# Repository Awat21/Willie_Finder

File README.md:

# Willie_Finder
Cat tracker using LORA

- [BOM.md](BOM.md) - parts list with links
- [case/](case/) - collar pod case model (STEP, STL, CadQuery source)
- [pcb/](pcb/) - custom single-board tracker: schematic and first-pass layout (KiCad 9)

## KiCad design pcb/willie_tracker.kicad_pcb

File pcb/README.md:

# Custom tracker PCB

Draft schematic (rev 0.4) and a first-pass board layout for a single-board version of the collar tracker. **Not ready for fabrication.**

- `willie_tracker.kicad_sch`, `willie_tracker.kicad_pro`, `sym-lib-table` - KiCad 9 project (needs KiCad 9 or newer).
- `willie_tracker.pdf` - the same schematic as a PDF.
- `willie.kicad_sym` - project symbol library (RAK4630).
- `gen_schematic.py`, `sexpr.py` - generator; the parts and net table at the top of `gen_schematic.py` are the source.
- `willie_tracker.net` - netlist exported by KiCad from the schematic.
- `check_netlist.py` - regenerates, exports the netlist with `kicad-cli`, compares it to the net table, checks the stacked pads, runs ERC and exports the PDF.
- `erc_report.txt` - KiCad's electrical rule check report.
- `willie_tracker.kicad_pcb` - first-pass board layout (KiCad 9).
- `willie.pretty/RAK4630.kicad_mod`, `fp-lib-table` - RAK4630 land pattern, drawn from RAK's datasheet drawings.
- `gen_layout.py` - places the parts (the placement table at the top is the source). `route.py` - grid autorouter with rip-up and re-route. Run both with the Python that has KiCad's `pcbnew` module: `/usr/bin/python3 route.py`.
- `drc_report.txt` - KiCad's design rule check report for the layout.
- `willie_tracker_board.step` - bare board (outline and holes, no component bodies) for CAD.
- `renders/` - top and bottom views of the board.

## What is on it

| Block | Part | Notes |
|---|---|---|
| MCU + LoRa + Bluetooth | RAK4630 (-I variant with U.FL sockets) | Same pins as the Meshtastic `rak4631` variant |
| GNSS | u-blox MAX-M10S, U.FL socket for a passive antenna | UART on P0.15/P0.16, PPS on P0.17 |
| GNSS power switch | TPS22917 | Enabled by P1.02 (the firmware's `PIN_3V3_EN`) |
| Accelerometer | LIS3DH, I2C 0x18 | INT1 on P1.01 |
| Charger and power path | MCP73871, 100 mA USB input limit | Runs the system from USB while charging; battery supplements peaks. Amber LED while charging |
| Regulator | XC6220 3.3 V | Fed from VSYS (USB when plugged in, otherwise the battery) |
| GNSS signal buffer | 74LVC3G34 on the switched rail | Isolates TX, RX and PPS when the GNSS is off |
| Battery sense | 1M / 1.5M divider on P0.05 | Matches the RAK base boards |
| USB | GCT USB4110 USB-C (all surface-mount) with CC resistors and USBLC6 ESD protection | Charging and firmware updates |

## Review status (rev 0.3)

Response to the rev 0.2 schematic review:

| Finding | Status |
|---|---|
| 1. U6 and U7 ground pads unverified | Verified in the native netlist (`willie_tracker.net`, exported by KiCad): U6.1, U6.10, U6.12, U7.5, U7.10 and U7.12 are all on GND. `check_netlist.py` now asserts these and the other stacked pads on every run, and the schematic lists the stacked pins in a note. The library footprints (`RF_GPS:ublox_MAX`, `Package_LGA:LGA-16_3x3mm_P0.5mm_LayoutBorder3x5y`) contain pads 1-18 and 1-16. ERC has since been run; see below. |
| 2. USB inrush and current budget | Changed: the MCP73831 and the discrete load sharing are replaced by an MCP73871 power-path charger. SEL and PROG2 are tied low, which limits total USB input current to 100 mA (80-100 mA per the datasheet). Above that the battery supplements the load through the internal ideal diode. Only C1 (4.7 uF) is directly on VBUS; C3 is behind the current limit. |
| 3. Battery handover and VBUS leakage | Removed with the discrete circuit: Q1, D3 and R13 are gone. Handover is inside the MCP73871. |

Earlier fixes kept: regulator capacitors (10 uF / 4.7 uF), GNSS buffer U8, passive-antenna note.

MCP73871 pin settings, checked against Microchip DS20002090E: SEL low = USB input; PROG2 low = 100 mA; THERM 10k to VSS = no thermistor; VPCC tied to IN = disabled; TE low = safety timer enabled; CE high = charging enabled; PROG1 13k = 77 mA; PROG3 100k = 10 mA termination.

## Board layout (first pass)

| | |
|---|---|
| Size | 25.0 x 44.0 mm rectangle, 0.8 mm thick |
| Assembly | Every part is surface-mount and on the top side. The bottom is bare, so the board can sit flat on a hot plate |
| Through-holes | No plated through-hole pads. Two unplated locating holes for the USB-C connector's pegs |
| Layers | 4: top (parts and signals), inner 1 (solid ground plane), inner 2 (signals plus a 3.3 V pour), bottom (signals plus a ground pour) |
| Assembled thickness | About 4 mm: USB-C connector roughly 3.2 mm on a 0.8 mm board (estimate from datasheet heights) |
| Rules | 0.2 mm tracks, 0.15 mm clearance, 0.6 / 0.3 mm vias, tented |
| Routing | 933 track segments, 146 vias, every net connected |
| KiCad DRC | 0 errors, 0 unconnected pads, 0 schematic parity issues, 1 library-sync warning on J1 (`drc_report.txt`) |

Changes for single-sided assembly (schematic rev 0.4):

- USB-C connector is now the GCT USB4110 (all surface-mount shell tabs) instead of a part with through-hole legs.
- The battery leads solder to two 1.5 x 3 mm surface pads (J2 BAT+, J4 BAT-) instead of through-hole wire pads.
- The five test pads moved to the top side.
- Length grew from 40 to 44 mm, the top of the allowed range, to give the small parts room for their vias.

The routing was done by `route.py`, a simple autorouter written for this board. It satisfies the clearance rules but
has had no engineering review. Before fabrication:

1. All tracks are 0.2 mm, including power (VBUS, VSYS, +BATT, +3V3). Widen the power tracks.
2. GNSS_RF is a short 0.2 mm track, not a calculated 50 ohm line. Set its width from the board house's stackup.
3. Tracks and tented vias run under the RAK4630. Check RAK's layout guidance for keep-out areas under the module.
4. Decoupling capacitors were placed for fit, not for shortest loop to their pins. Review each one.
5. USB D+ and D- are routed as two ordinary tracks, not a matched pair. Acceptable at full speed over this length; confirm.
6. Ground is poured on inner layer 1 and the bottom; the top has no pour. The 3.3 V pour on inner layer 2 is broken up by signal tracks.
7. The RAK4630 land pattern was drawn from the dimensions in RAK's datasheet images. Check it against a real module or RAK's own footprint before ordering.
8. Reference designators are hidden on the silkscreen; there is no silkscreen artwork, fiducials or mounting features.
9. USB-C sits at one short edge; the connector's exact overhang past the board edge is not checked.
10. Check that the USB4110's locating pegs do not stick out below a 0.8 mm board; if they do, the board will not sit flat on a hot plate (use a thicker board or trim the pegs).
11. Surface-mount battery pads can peel under wire strain. Glue or otherwise strain-relieve the leads.
12. The render shows via rings exposed although tenting is set in the board file; confirm in the Gerbers.
13. Tracks and vias also run under the MAX-M10S; check u-blox's layout guidance for the area under the module.
14. The J1 library-sync warning in DRC is unexplained; the pads and nets match the schematic.

## Electrical rule check

Run with `kicad-cli` 9.0.9, all severities. Two items remain, both intended:

| Item | Severity | Explanation |
|---|---|---|
| U4 QOD (open collector) tied to VOUT (power output) | error | Confirmed against TI's TPS22917 datasheet (section 9.3.3): shorting QOD to VOUT is one of the three documented configurations and uses the internal discharge resistance. CT left open is also a documented option. KiCad flags the pin types only. |
| U7 SDO/SA0 (bidirectional) on GND | warning | Intended: address-select pin tied low for I2C address 0x18. |

No unconnected pins, undriven power pins or conflicting outputs were reported.

## Confirmed since rev 0.3

- TPS22917 QOD to VOUT: confirmed (above). Its DBV pinout in the datasheet matches the KiCad symbol.
- RAK4630 supply pins: RAK's reference schematic states that for a single 3.3 V supply VBAT_NRF, VDD_NRF, VBAT_SX and VBAT_IO_SX are all connected to 3.3 V, as drawn here.
- RAK4630 pin order: RAK's pinout drawing matches the land pattern (pin 1 at the top-right of the top row, counting anticlockwise).
- VBUS capacitance: RAK's schematic shows a 4.7 uF capacitor on VBUS inside the module. With C1 that is 9.4 uF nominal directly on VBUS, just under the 10 uF limit.

## Open items

1. USB charge current: the datasheet says PROG1 sets fast charge when SEL is high. With SEL low the charge current may follow the 100 mA USB limit rather than the 77 mA resistor setting. Confirm, and check either value against the chosen cell's rating.
2. Charger variant: -2CC is a first pick (4.20 V). Confirm its timer period and low-battery-indicator options.
3. VBUS capacitance is 9.4 uF nominal against a 10 uF limit; decide whether to reduce C1.
4. With USB connected the regulator input (VSYS) follows VBUS, about 5 V. Confirm against the XC6220 rating.
5. U8 relies on the 74LVC family's powered-off protection. The review confirmed this for the Nexperia part; use that manufacturer or re-check.
6. LIS3DH unused ADC pins are tied to ground; confirm against the datasheet.
7. The layout items listed under "Board layout" above.

## To verify on a prototype

- Charge termination with the tracker running on USB, and USB attach, detach and cold boot on each kind of port you intend to support (including a plain USB 2.0 port or hub).
- The 3.3 V rail on a scope with a partly discharged cell during GNSS startup, LoRa transmit, and both together.
- GNSS RX pin voltage and switched-rail current with the GNSS off, during reset, and across several on/off cycles. Confirm 3V3_GNSS discharges on shutdown and that UART and PPS behave through power transitions.
- GNSS reception with the actual passive antenna in the enclosure; route GNSS_RF as a 50 ohm trace.

## Firmware checks

- GNSS enable is expected active-high on Arduino pin 34 (P1.02); confirm with the intended Meshtastic build.
- Battery reading: the 1M / 1.5M divider is nominally x1.667 and the RAK4631 firmware uses x1.73, so a 4.20 V cell may read about 0.16 V high. Calibrate against a meter.
- LIS3DH INT1 is wired to P1.01, but the stock Meshtastic driver polls over I2C. Wake-on-motion from deep sleep needs firmware support.

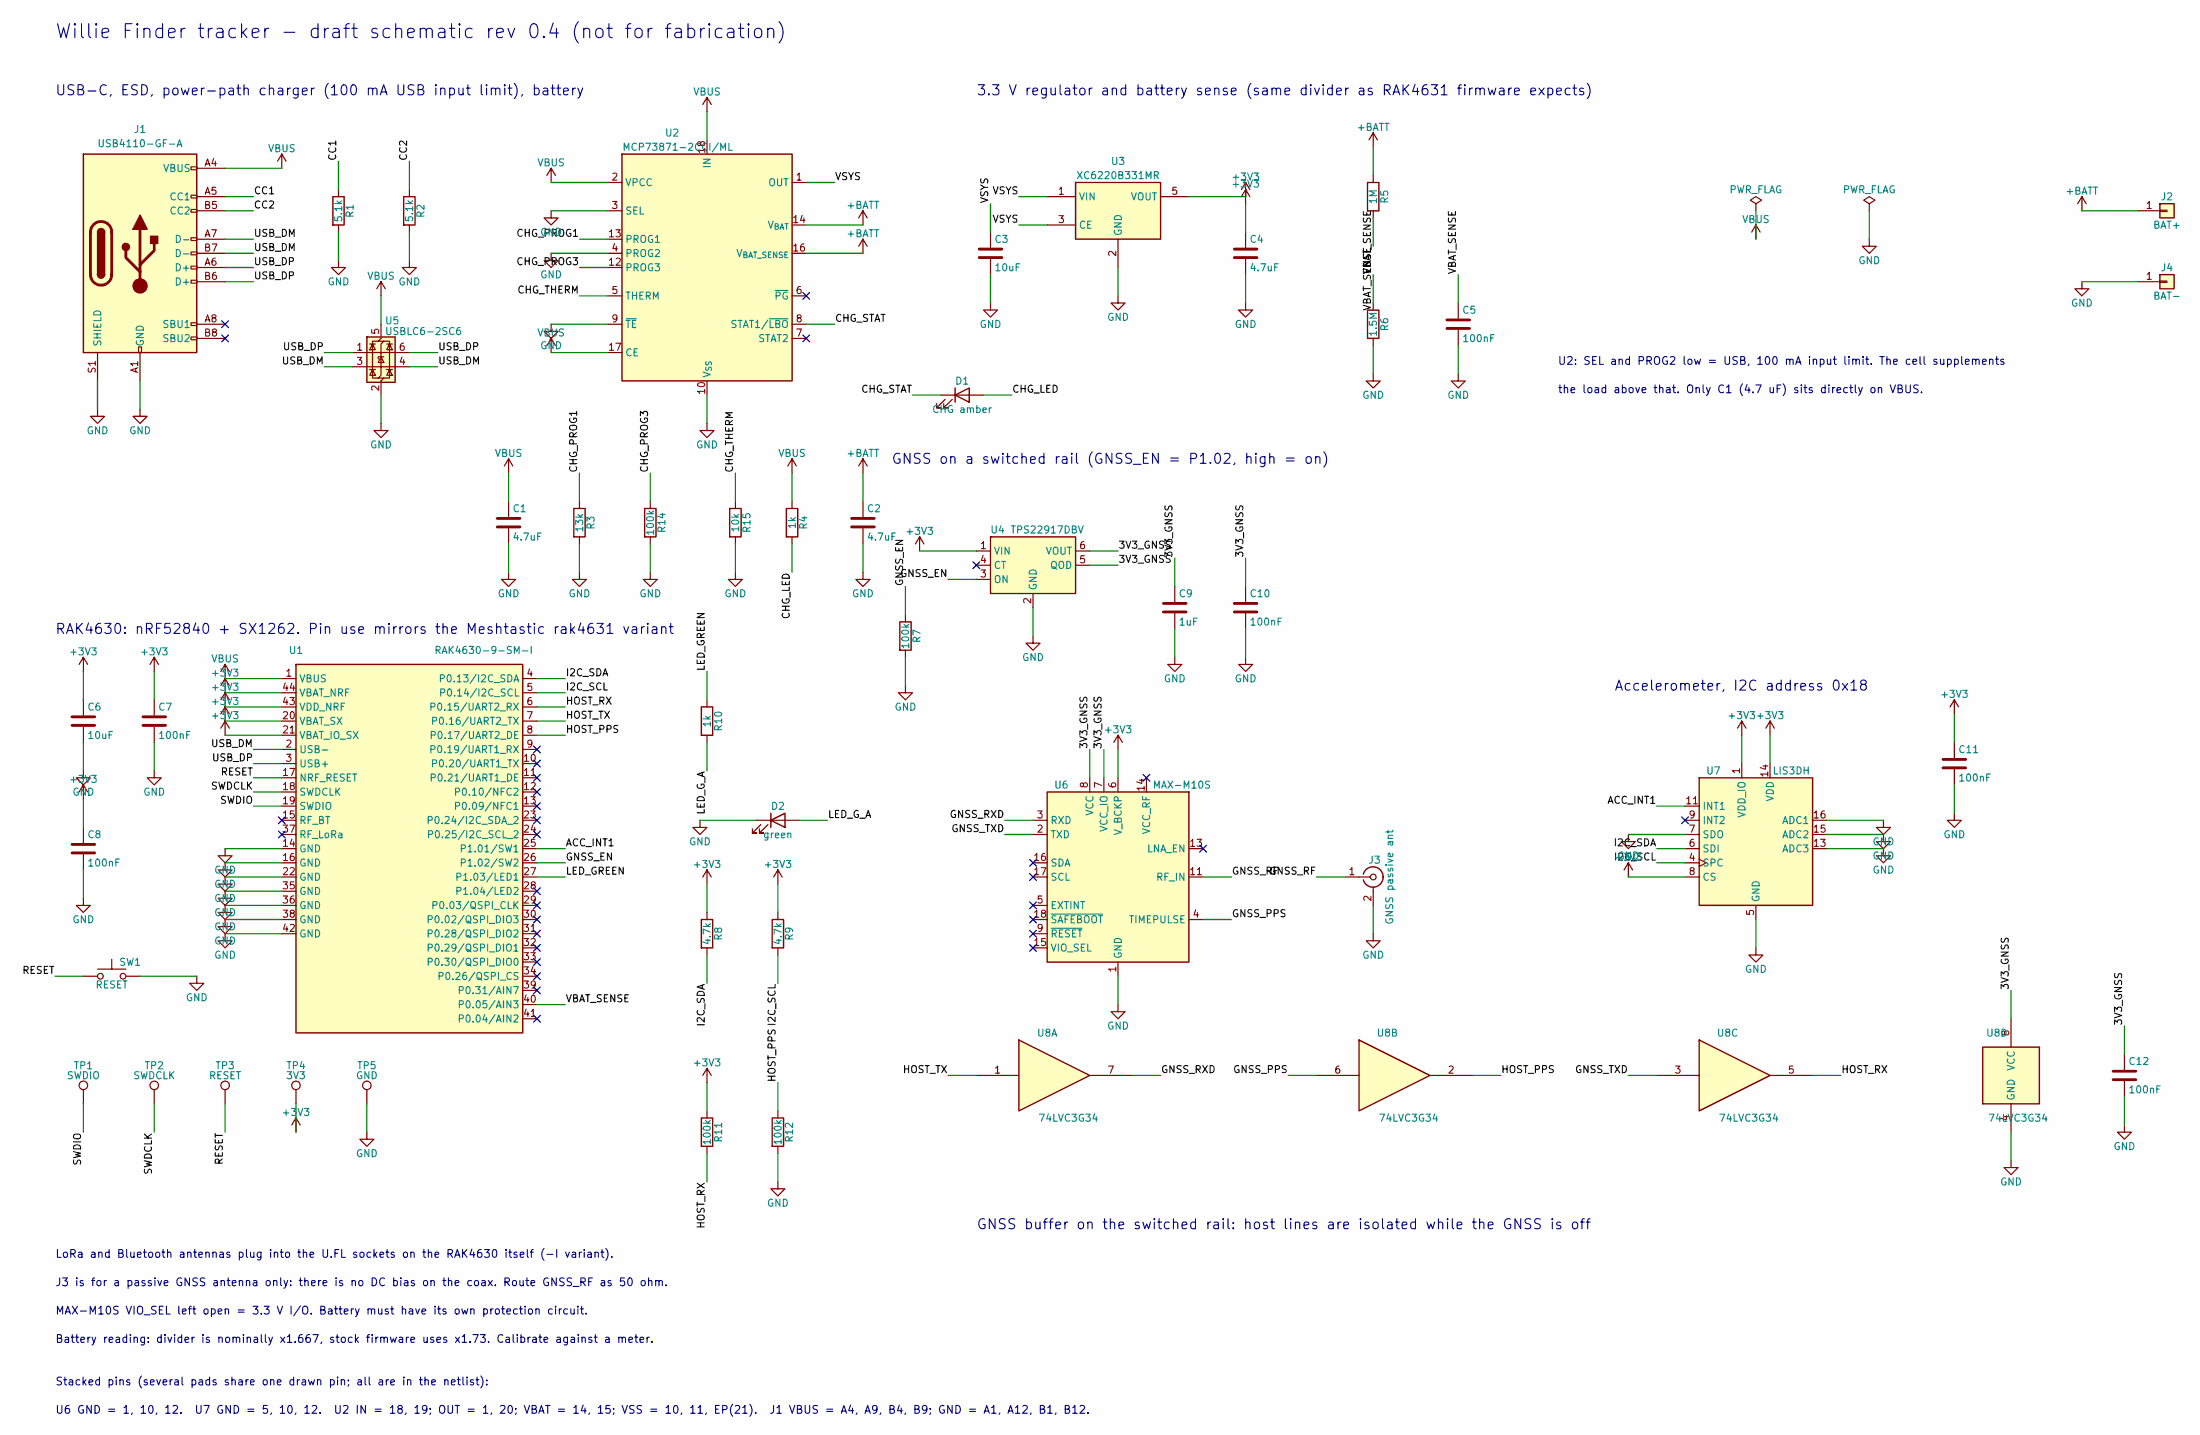
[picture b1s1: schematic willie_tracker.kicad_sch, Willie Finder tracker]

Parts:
C1, C2: 4.7uF; C_0603_1608Metric
C3, C6: 10uF; C_0603_1608Metric
C4: 4.7uF; C_0402_1005Metric
C5, C7, C8, C10, C11, C12: 100nF; C_0402_1005Metric
C9: 1uF; C_0402_1005Metric
D1: CHG amber; LED_0402_1005Metric
D2: green; LED_0402_1005Metric
J1: USB4110-GF-A; USB_C_Receptacle_GCT_USB4110
J2: BAT+; SolderWirePad_1x01_SMD_1.5x3mm
J3: GNSS passive ant; U.FL_Hirose_U.FL-R-SMT-1_Vertical
J4: BAT-; SolderWirePad_1x01_SMD_1.5x3mm
R1, R2: 5.1k; R_0402_1005Metric
R3: 13k; R_0402_1005Metric
R4, R10: 1k; R_0402_1005Metric
R5: 1M; R_0402_1005Metric
R6: 1.5M; R_0402_1005Metric
R7, R11, R12, R14: 100k; R_0402_1005Metric
R8, R9: 4.7k; R_0402_1005Metric
R15: 10k; R_0402_1005Metric
SW1: RESET; SW_SPST_B3U-1000P
TP1: SWDIO; TestPoint_Pad_D1.0mm
TP2: SWDCLK; TestPoint_Pad_D1.0mm
TP3: RESET; TestPoint_Pad_D1.0mm
TP4: 3V3; TestPoint_Pad_D1.0mm
TP5: GND; TestPoint_Pad_D1.0mm
U1: RAK4630-9-SM-I; RAK4630
U2: MCP73871-2CCI/ML; QFN-20-1EP_4x4mm_P0.5mm_EP2.5x2.5mm
U3: XC6220B331MR; SOT-23-5
U4: TPS22917DBV; SOT-23-6
U5: USBLC6-2SC6; SOT-23-6
U6: MAX-M10S; ublox_MAX
U7: LIS3DH; LGA-16_3x3mm_P0.5mm_LayoutBorder3x5y
U8: 74LVC3G34; VSSOP-8_2.3x2mm_P0.5mm

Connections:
+3V3: C4.1, C6.1, C7.1, C8.1, C11.1, R8.1, R9.1, R11.1, TP4.1, U1.20 (VBAT_SX), U1.21 (VBAT_IO_SX), U1.43 (VDD_NRF), U1.44 (VBAT_NRF), U3.5 (VOUT), U4.1 (VIN), U6.6 (V_BCKP), U7.1 (VDD_IO), U7.8 (CS), U7.14 (VDD)
+BATT: C2.1, J2.1, R5.1, U2.14 (V_{BAT}), U2.15 (V_{BAT}), U2.16 (V_{BAT_SENSE})
/3V3_GNSS: C9.1, C10.1, C12.1, U4.5 (QOD), U4.6 (VOUT), U6.7 (VCC_IO), U6.8 (VCC), U8.8 (VCC)
/ACC_INT1: U1.25 (P1.01/SW1), U7.11 (INT1)
/CC1: J1.A5 (CC1), R1.1
/CC2: J1.B5 (CC2), R2.1
/CHG_LED: D1.2 (A), R4.2
/CHG_PROG1: R3.1, U2.13 (PROG1)
/CHG_PROG3: R14.1, U2.12 (PROG3)
/CHG_STAT: D1.1 (K), U2.8 (STAT1/~LBO)
/CHG_THERM: R15.1, U2.5 (THERM)
/GNSS_EN: R7.1, U1.26 (P1.02/SW2), U4.3 (ON)
/GNSS_PPS: U6.4 (TIMEPULSE), U8.6
/GNSS_RF: J3.1 (In), U6.11 (RF_IN)
/GNSS_RXD: U6.3 (RXD), U8.7
/GNSS_TXD: U6.2 (TXD), U8.3
/HOST_PPS: R12.1, U1.8 (P0.17/UART2_DE), U8.2
/HOST_RX: R11.2, U1.6 (P0.15/UART2_RX), U8.5
/HOST_TX: U1.7 (P0.16/UART2_TX), U8.1
/I2C_SCL: R9.2, U1.5 (P0.14/I2C_SCL), U7.4 (SPC)
/I2C_SDA: R8.2, U1.4 (P0.13/I2C_SDA), U7.6 (SDI)
/LED_GREEN: R10.1, U1.27 (P1.03/LED1)
/LED_G_A: D2.2 (A), R10.2
/RESET: SW1.1, TP3.1, U1.17 (NRF_RESET)
/SWDCLK: TP2.1, U1.18 (SWDCLK)
/SWDIO: TP1.1, U1.19 (SWDIO)
/USB_DM: J1.A7 (D-), J1.B7 (D-), U1.2 (USB-), U5.3 (I/O2), U5.4 (I/O2)
/USB_DP: J1.A6 (D+), J1.B6 (D+), U1.3 (USB+), U5.1 (I/O1), U5.6 (I/O1)
/VBAT_SENSE: C5.1, R5.2, R6.1, U1.40 (P0.05/AIN3)
/VSYS: C3.1, U2.1 (OUT), U2.20 (OUT), U3.1 (VIN), U3.3 (CE)
GND: C1.2, C2.2, C3.2, C4.2, C5.2, C6.2, C7.2, C8.2, C9.2, C10.2, C11.2, C12.2, D2.1 (K), J1.A1 (GND), J1.A12 (GND), J1.B1 (GND), J1.B12 (GND), J1.S1 (SHIELD), J3.2 (Ext), J4.1, R1.2, R2.2, R3.2, R6.2, R7.2, R12.2, R14.2, R15.2, SW1.2, TP5.1, U1.14 (GND), U1.16 (GND), U1.22 (GND), U1.35 (GND), U1.36 (GND), U1.38 (GND), U1.42 (GND), U2.3 (SEL), U2.4 (PROG2), U2.9 (~TE), U2.10 (V_{SS}), U2.11 (V_{SS}), U2.21 (V_{SS}), U3.2 (GND), U4.2 (GND), U5.2 (GND), U6.1 (GND), U6.10 (GND), U6.12 (GND), U7.5 (GND), U7.7 (SDO), U7.10 (GND), U7.12 (GND), U7.13 (ADC3), U7.15 (ADC2), U7.16 (ADC1), U8.4 (GND)
VBUS: C1.1, J1.A4 (VBUS), J1.A9 (VBUS), J1.B4 (VBUS), J1.B9 (VBUS), R4.1, U1.1 (VBUS), U2.2 (VPCC), U2.17 (CE), U2.18 (IN), U2.19 (IN), U5.5 (VBUS)

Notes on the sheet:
Willie Finder tracker - draft schematic rev 0.4 (not for fabrication)
USB-C, ESD, power-path charger (100 mA USB input limit), battery
3.3 V regulator and battery sense (same divider as RAK4631 firmware expects)
RAK4630: nRF52840 + SX1262. Pin use mirrors the Meshtastic rak4631 variant
GNSS on a switched rail (GNSS_EN = P1.02, high = on)
Accelerometer, I2C address 0x18
GNSS buffer on the switched rail: host lines are isolated while the GNSS is off
LoRa and Bluetooth antennas plug into the U.FL sockets on the RAK4630 itself (-I variant).
J3 is for a passive GNSS antenna only: there is no DC bias on the coax. Route GNSS_RF as 50 ohm.
MAX-M10S VIO_SEL left open = 3.3 V I/O. Battery must have its own protection circuit.
Battery reading: divider is nominally x1.667, stock firmware uses x1.73. Calibrate against a meter.
Stacked pins (several pads share one drawn pin; all are in the netlist):
U6 GND = 1, 10, 12. U7 GND = 5, 10, 12. U2 IN = 18, 19; OUT = 1, 20; VBAT = 14, 15; VSS = 10, 11, EP(21). J1 VBUS = A4, A9, B4, B9; GND = A1, A12, B1, B12.
U2: SEL and PROG2 low = USB, 100 mA input limit. The cell supplements
the load above that. Only C1 (4.7 uF) sits directly on VBUS.

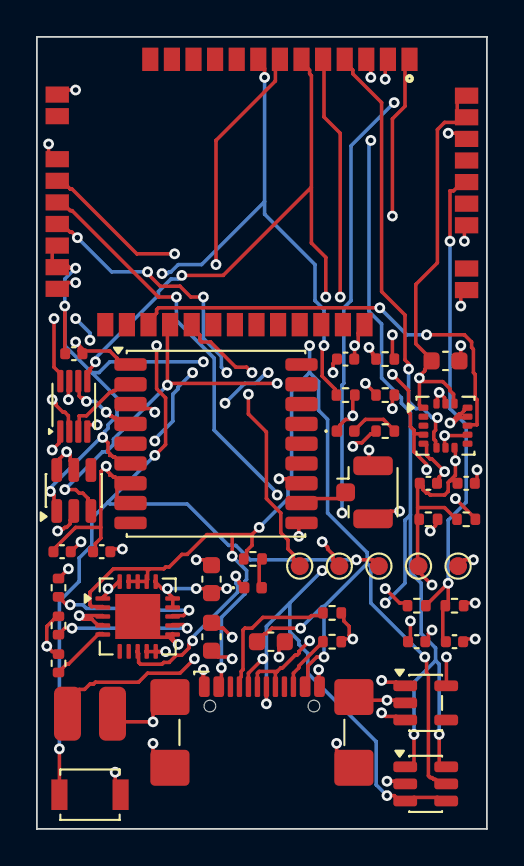
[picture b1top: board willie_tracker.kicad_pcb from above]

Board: 4 copper layers, 25.0 x 44.0 mm, 46 parts (0 on the bottom side), 32 nets.
